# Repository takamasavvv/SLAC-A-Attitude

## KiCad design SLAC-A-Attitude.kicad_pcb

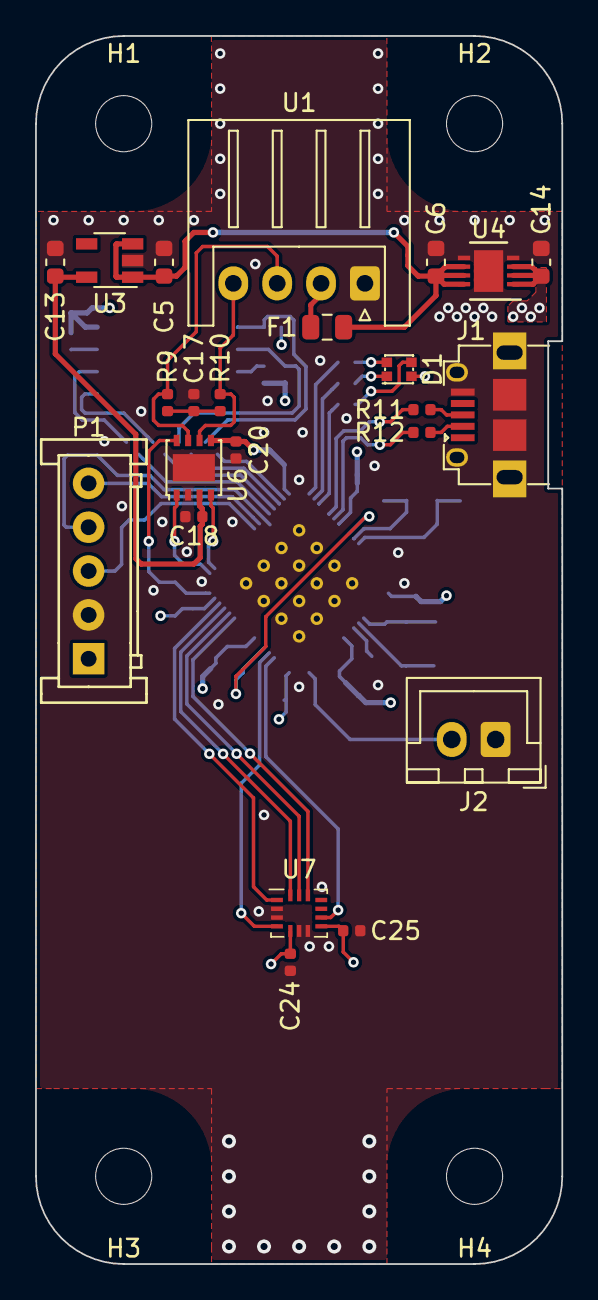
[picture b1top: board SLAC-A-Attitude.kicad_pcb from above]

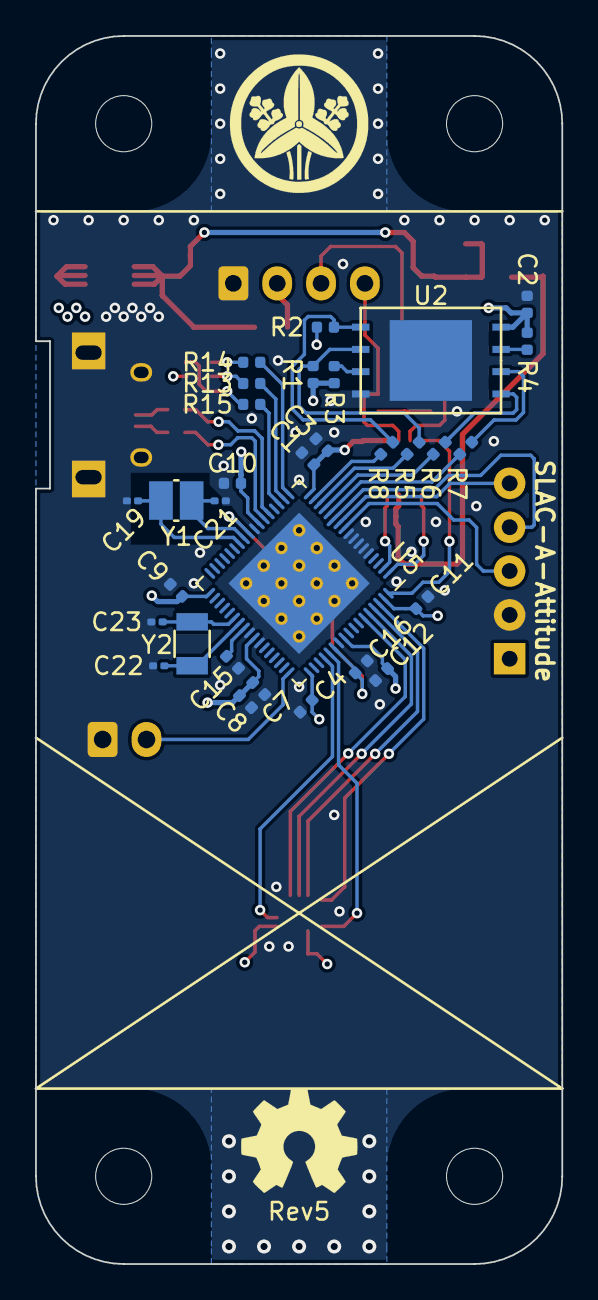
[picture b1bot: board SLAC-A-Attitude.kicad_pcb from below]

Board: 4 copper layers, 30.0 x 70.0 mm, 58 parts (31 on the bottom side), 47 nets.

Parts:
C1, C2, C3, C4, C7, C8, C9, C11, C18, C20, C25: 0.1uF; C_0402_1005Metric
C5, C6, C13, C14: 10uF; C_0603_1608Metric
C10, C12, C15, C16, C24: 1uF; C_0402_1005Metric
C17: 4.7nF; C_0402_1005Metric
C19, C21, C22, C23: 9pF; C_0201_0603Metric
D1: LED_RGBA; LED_LiteOn_LTST-C19HE1WT
F1: Polyfuse; Fuse_0805_2012Metric
H1, H2, H3, H4: MountingHole; MountingHole_3.2mm_M3
J1: USB_B_Micro; Hirose_ZX_ZX62D-B-5P8
J2: Conn_01x02; JST_XH_B2B-XH-A_1x02_P2.50mm_Vertical
P1: KRC_Conn_SWD; JST_JQ_05JQ-BT_1x05_P2.5mm_Vertical
R1, R2, R3, R4: 4.7kΩ; R_0402_1005Metric
R5, R6, R7, R8, R11, R12: 22Ω; R_0402_1005Metric
R9, R10: 56Ω; R_0402_1005Metric
R13: 1.5kΩ; R_0402_1005Metric
R14, R15: 820Ω; R_0402_1005Metric
U1: KRC_Conn_CAN; JST_XH_S4B-XH-A_1x04_P2.50mm_Horizontal
U2: W25N01GVxxIG-IT; WSON-8_8x6mm_P1.27mm
U3: LT1761-5; TSOT-23-5
U4: LT1965xDD-3.3; DFN-8-1EP_3x3mm_P0.5mm_EP1.66x2.38mm
U5: CY8C58xxLTI-LPxxx; Cypress_QFN-68_EP_8x8_Pitch0.4mm
U6: NCV7342; DFN-8-1EP_3x3mm_P0.65mm_EP1.55x2.4mm
U7: BMX160; Bosch_LGA-14_3x2.5mm_P0.5mm
Y1: Crystal_MHz; Crystal_Murata_XRCHA
Y2: Crystal_kHz; Crystal_SeikoEpson_FC-135

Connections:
+3V3: C1.1, C2.1, C3.1, C4.1, C7.1, C8.1, C9.1, C10.1, C11.1, C12.1, C14.1, C20.1, C24.2, C25.1, D1.4, R1.1, R2.1, R3.1, R4.1, U2.8, U4.1, U4.2, U4.3, U5.17, U5.24, U5.35, U5.44, U5.52, U5.59, U5.67, U6.5, U7.5, U7.8
+5V: C13.1, C18.2, U3.5, U6.3
/AGM-INT1: U5.56, U7.4
/AGM-INT2: U5.55, U7.9
/AGM-MISO: U5.64, U7.13
/AGM-MOSI: U5.65, U7.14
/AGM-SCLK: U5.66, U7.1
/AGM-~CS: U5.63, U7.12
/CAN-RXD: U5.2, U6.4
/CAN-STB: U5.68, U6.8
/CAN-TXD: U5.1, U6.1
/Crystal_kHz_XI: C22.2, U5.41, Y2.1
/Crystal_kHz_XO: C23.2, U5.40, Y2.2
/External_IO: J2.2, U5.51
/Flash-MISO: R5.2, U5.15
/Flash-MOSI: R6.2, U5.14
/Flash-SCLK: R7.2, U5.13
/Flash-~CS: R8.2, U5.16
/LED-B: R15.2, U5.20
/LED-G: R14.2, U5.18
/LED-R: R13.2, U5.19
GND: C1.2, C2.2, C3.2, C4.2, C5.2, C6.2, C7.2, C8.2, C9.2, C10.2, C11.2, C12.2, C13.2, C14.2, C15.1, C16.1, C17.2, C18.1, C19.2, C20.2, C21.2, C22.1, C23.1, C24.1, C25.2, J1.5, J1.6, J2.1, P1.2, U1.1, U2.4, U2.9, U3.2, U4.4, U4.5, U4.9, U5.5, U5.6, U5.7, U5.8, U5.9, U5.25, U5.43, U5.45, U5.58, U5.69, U6.2, U6.9, U7.2, U7.3, U7.6, U7.7
unnamed: C5.1, C6.1, F1.1, U3.1, U3.3, U4.6, U4.7, U4.8
unnamed: C15.2, U5.42
unnamed: C16.2, U5.26, U5.57
unnamed: C17.1, R9.2, R10.1
unnamed: C19.1, U5.28, Y1.1
unnamed: C21.1, U5.27, Y1.2
unnamed: D1.1, R13.1
unnamed: D1.2, R14.1
unnamed: D1.3, R15.1
unnamed: J1.2, R12.1
unnamed: J1.3, R11.1
unnamed: P1.3, U5.10
unnamed: P1.4, U5.12
unnamed: P1.5, U5.11
unnamed: R1.2, R5.1, U2.2
unnamed: R2.2, R8.1, U2.1
unnamed: R3.2, U2.3
unnamed: R4.2, U2.7
unnamed: R6.1, U2.5
unnamed: R7.1, U2.6
unnamed: R9.1, U1.3, U6.7
unnamed: R10.2, U1.4, U6.6
unnamed: R11.2, U5.22
unnamed: R12.2, U5.23
VCC: F1.2, U1.2

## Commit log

2020-02-02 complete rev 5
